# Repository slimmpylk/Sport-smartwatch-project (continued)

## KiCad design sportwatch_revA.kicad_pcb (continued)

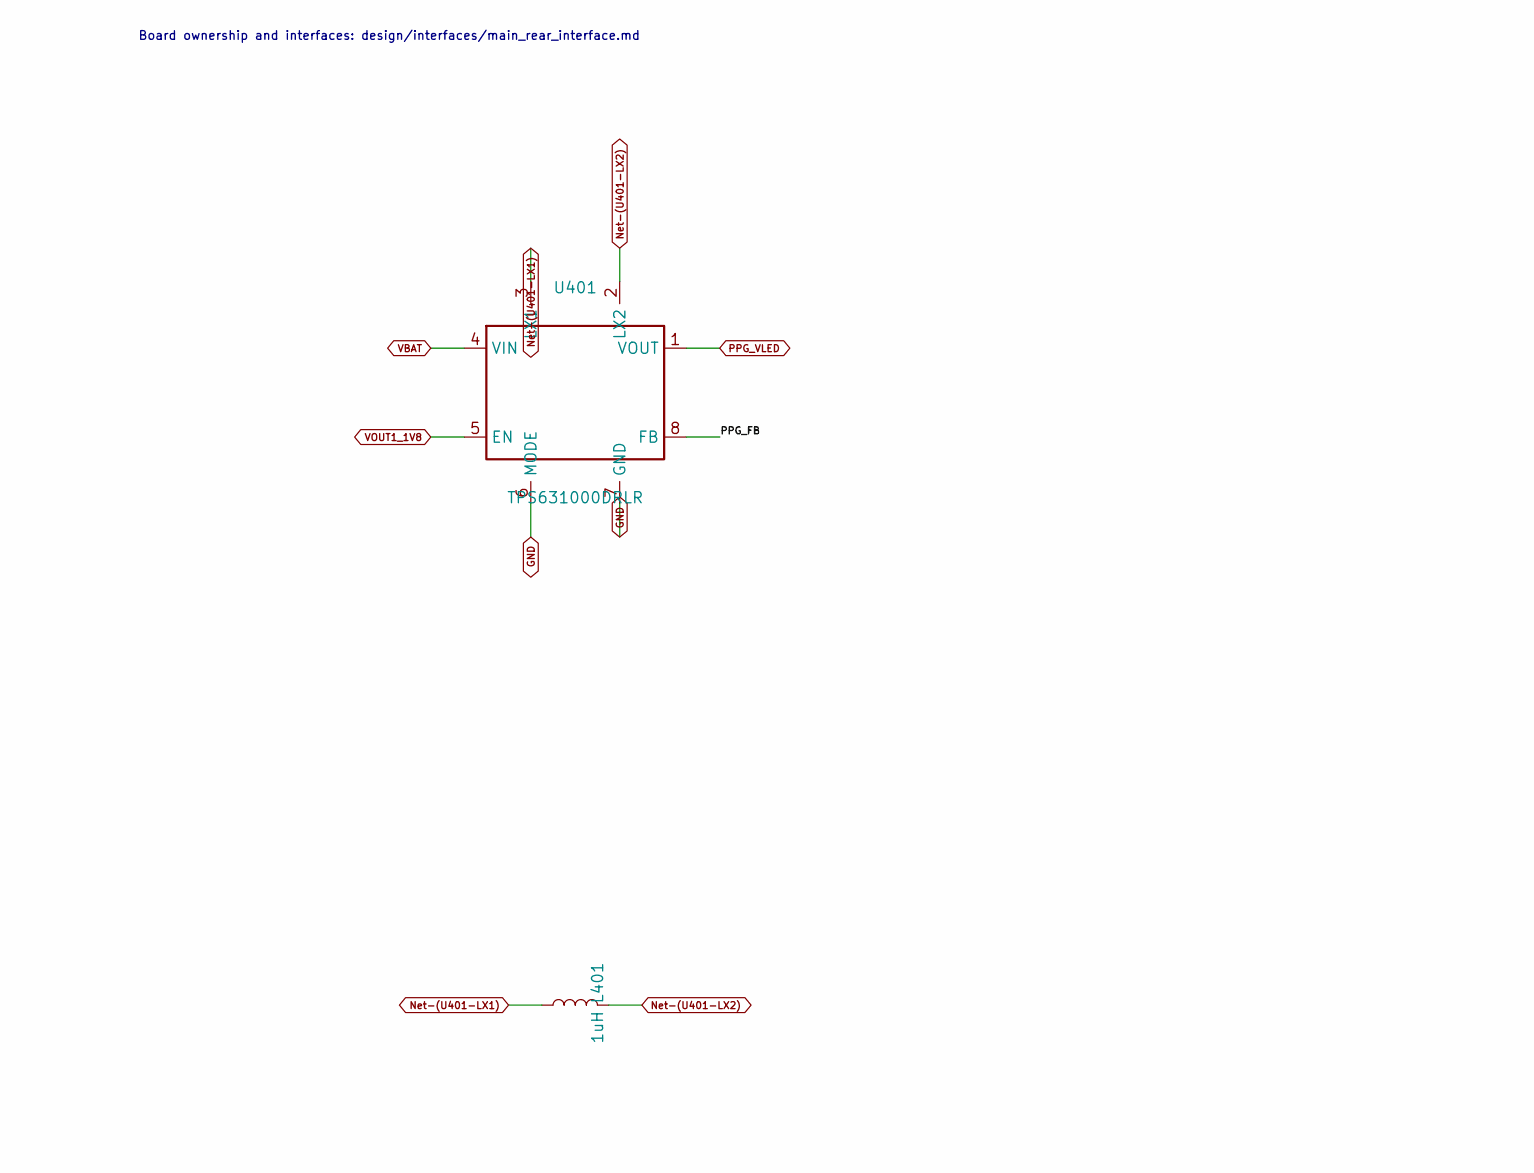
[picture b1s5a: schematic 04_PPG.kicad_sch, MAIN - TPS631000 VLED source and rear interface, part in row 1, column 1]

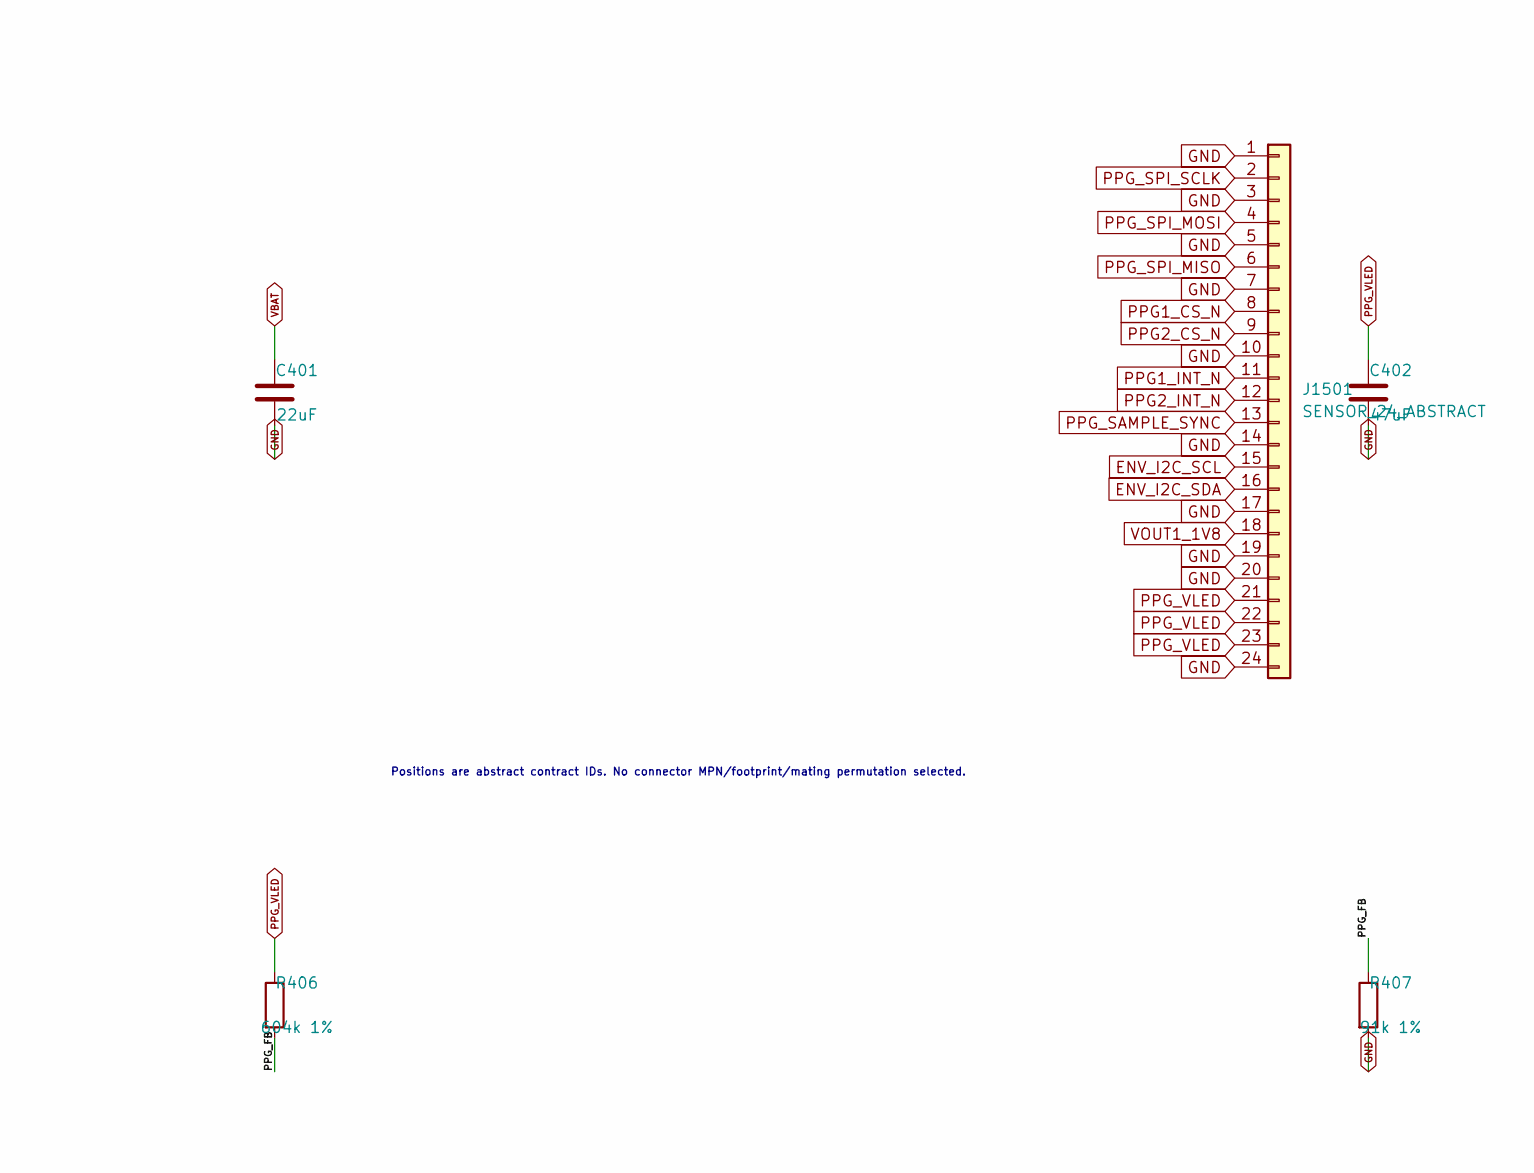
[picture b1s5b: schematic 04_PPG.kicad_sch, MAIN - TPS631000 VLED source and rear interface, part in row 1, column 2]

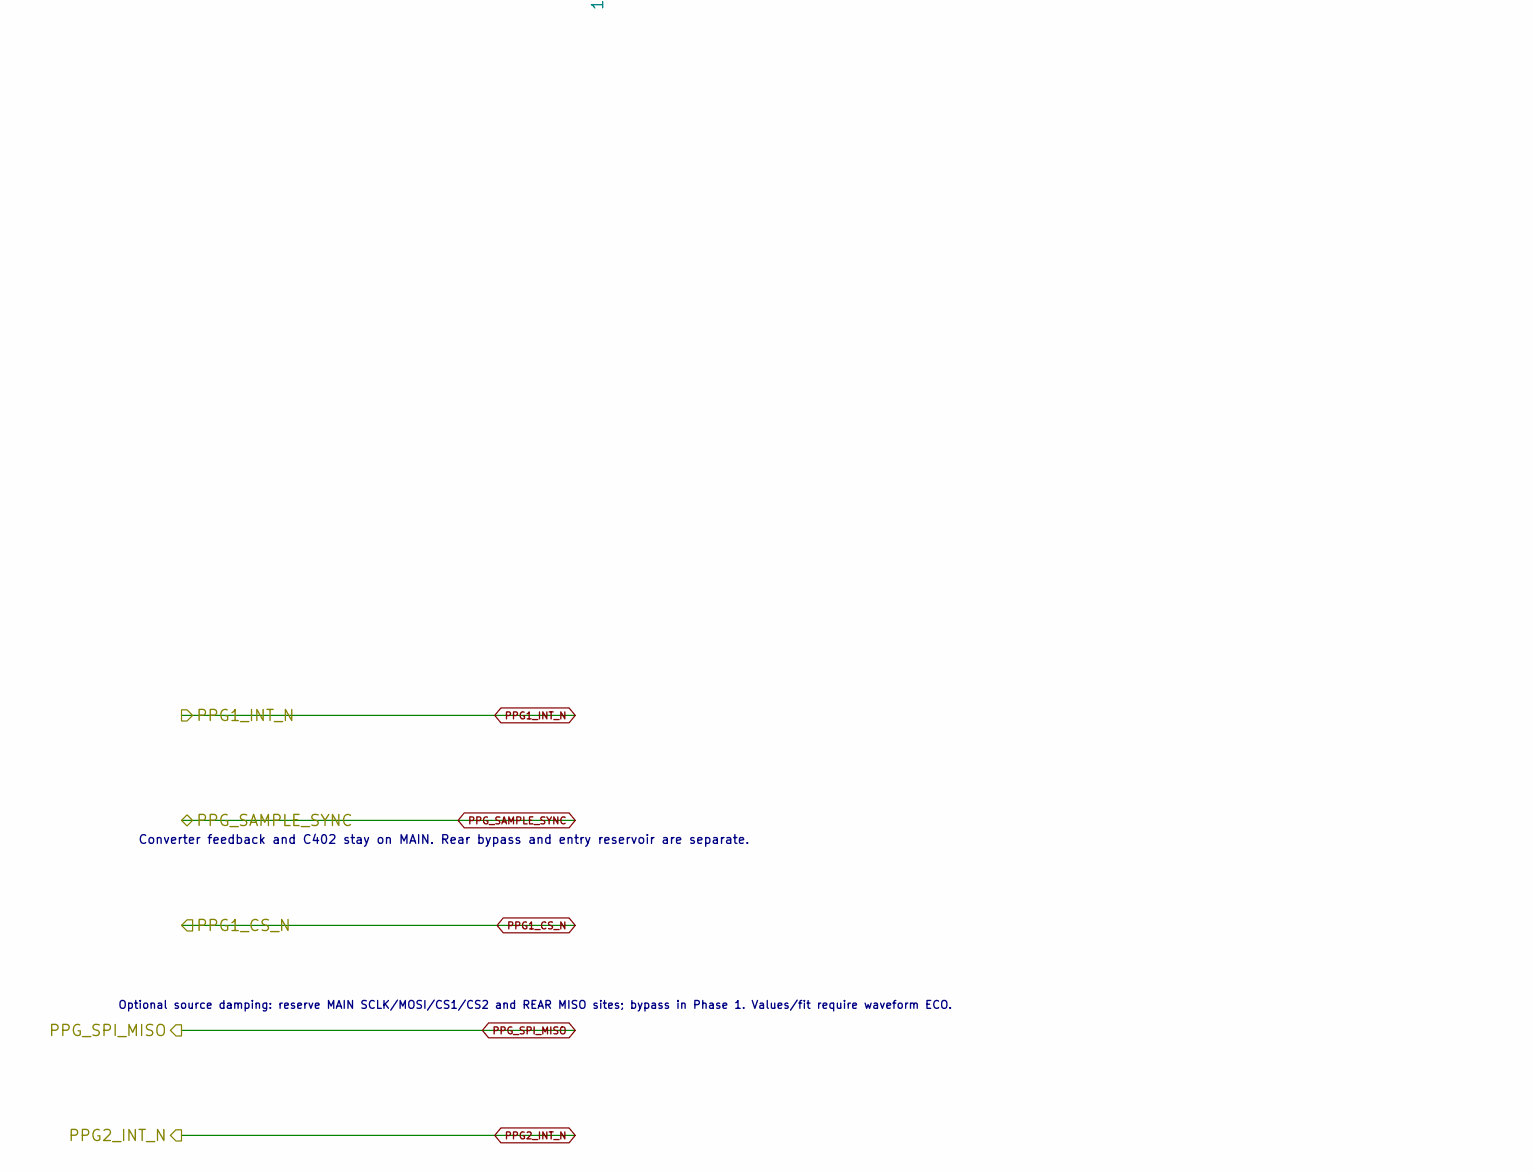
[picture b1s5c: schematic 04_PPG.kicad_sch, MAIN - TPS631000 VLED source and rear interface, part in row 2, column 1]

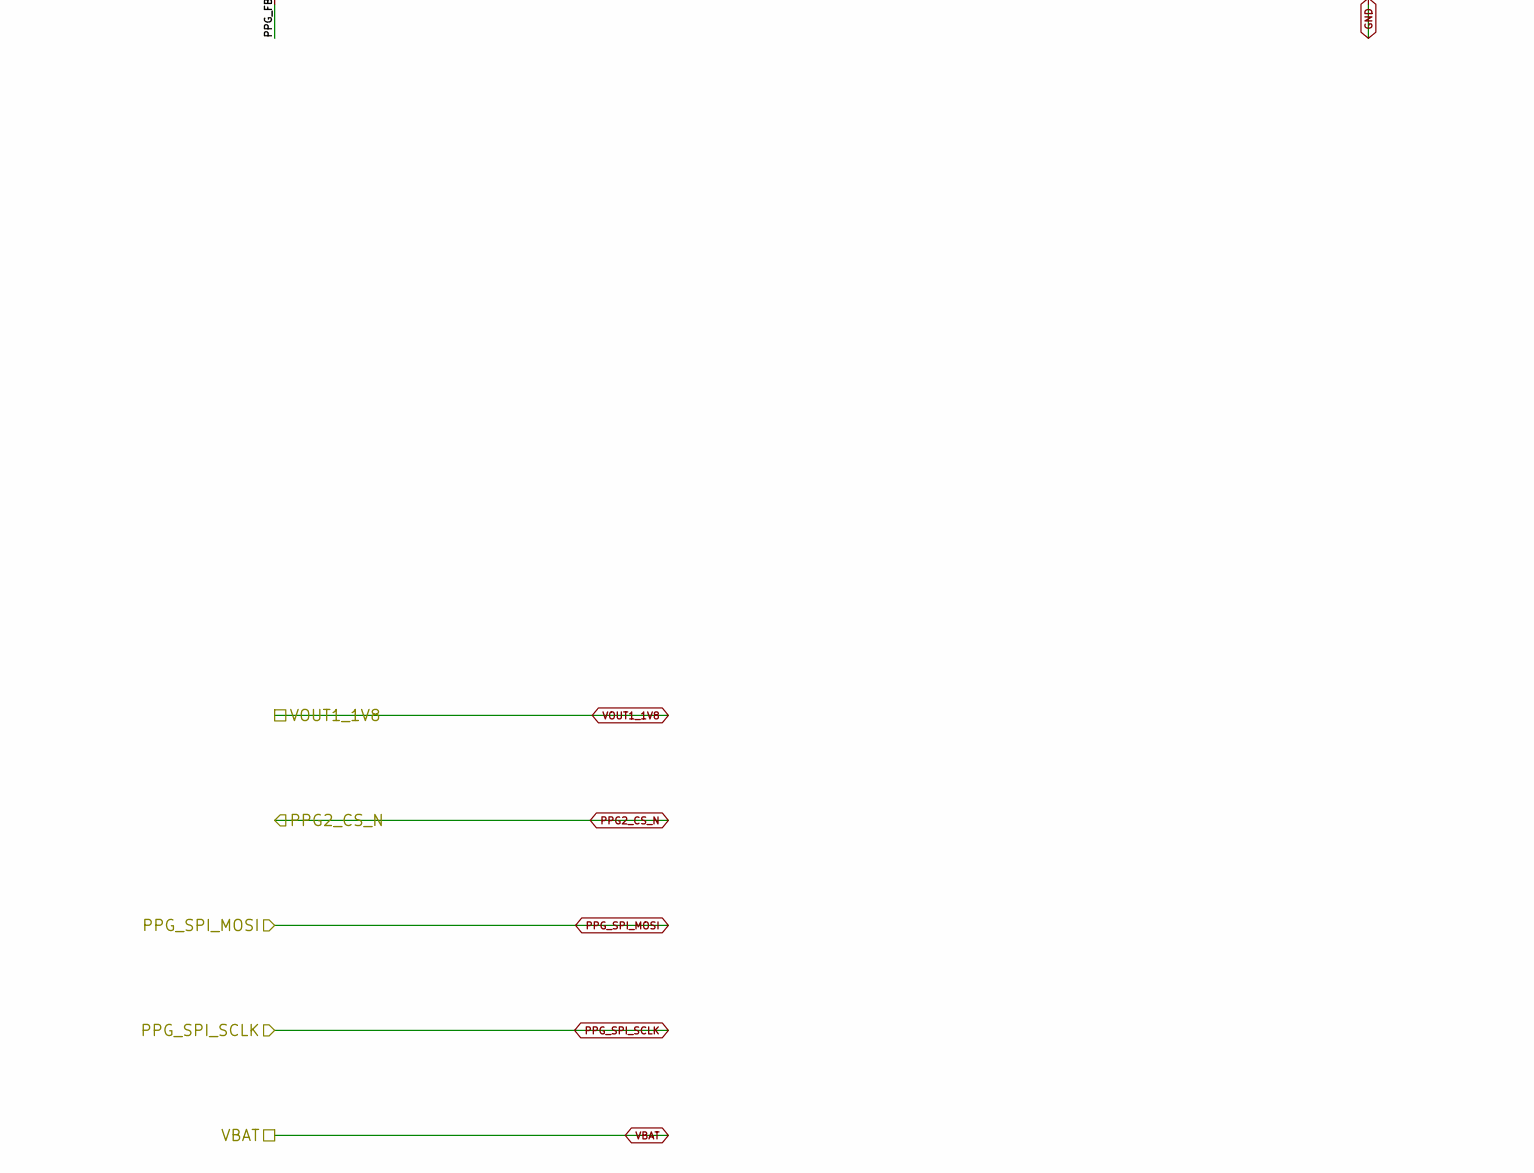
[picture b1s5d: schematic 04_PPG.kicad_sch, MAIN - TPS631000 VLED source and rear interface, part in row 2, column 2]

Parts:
C401: 22uF; C_0603_1608Metric
C402: 47uF; C_0805_2012Metric
J1501: SENSOR_24_ABSTRACT
L401: 1uH; L_2016_2016Metric
R406: 604k 1%; R_0402_1005Metric
R407: 91k 1%; R_0402_1005Metric
U401: TPS631000DRLR; SOT-583-8

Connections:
/04_PPG/PPG_FB: R406.2, R407.1, U401.8 (FB)
GND: C401.2, C402.2, J1501.1, J1501.3, J1501.5, J1501.7, J1501.10, J1501.14, J1501.17, J1501.19, J1501.20, J1501.24, R407.2, U401.6 (MODE), U401.7 (GND); also elsewhere on the board
unnamed: L401.1, U401.3 (LX1)
unnamed: L401.2, U401.2 (LX2)
PPG_VLED: C402.1, J1501.21, J1501.22, J1501.23, R406.1, U401.1 (VOUT)
VBAT: C401.1, U401.4 (VIN); also elsewhere on the board
VOUT1_1V8: J1501.18, U401.5 (EN); also elsewhere on the board

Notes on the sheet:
Board ownership and interfaces: design/interfaces/main_rear_interface.md
Converter feedback and C402 stay on MAIN. Rear bypass and entry reservoir are separate.
Positions are abstract contract IDs. No connector MPN/footprint/mating permutation selected.
Optional source damping: reserve MAIN SCLK/MOSI/CS1/CS2 and REAR MISO sites; bypass in Phase 1. Values/fit require waveform ECO.

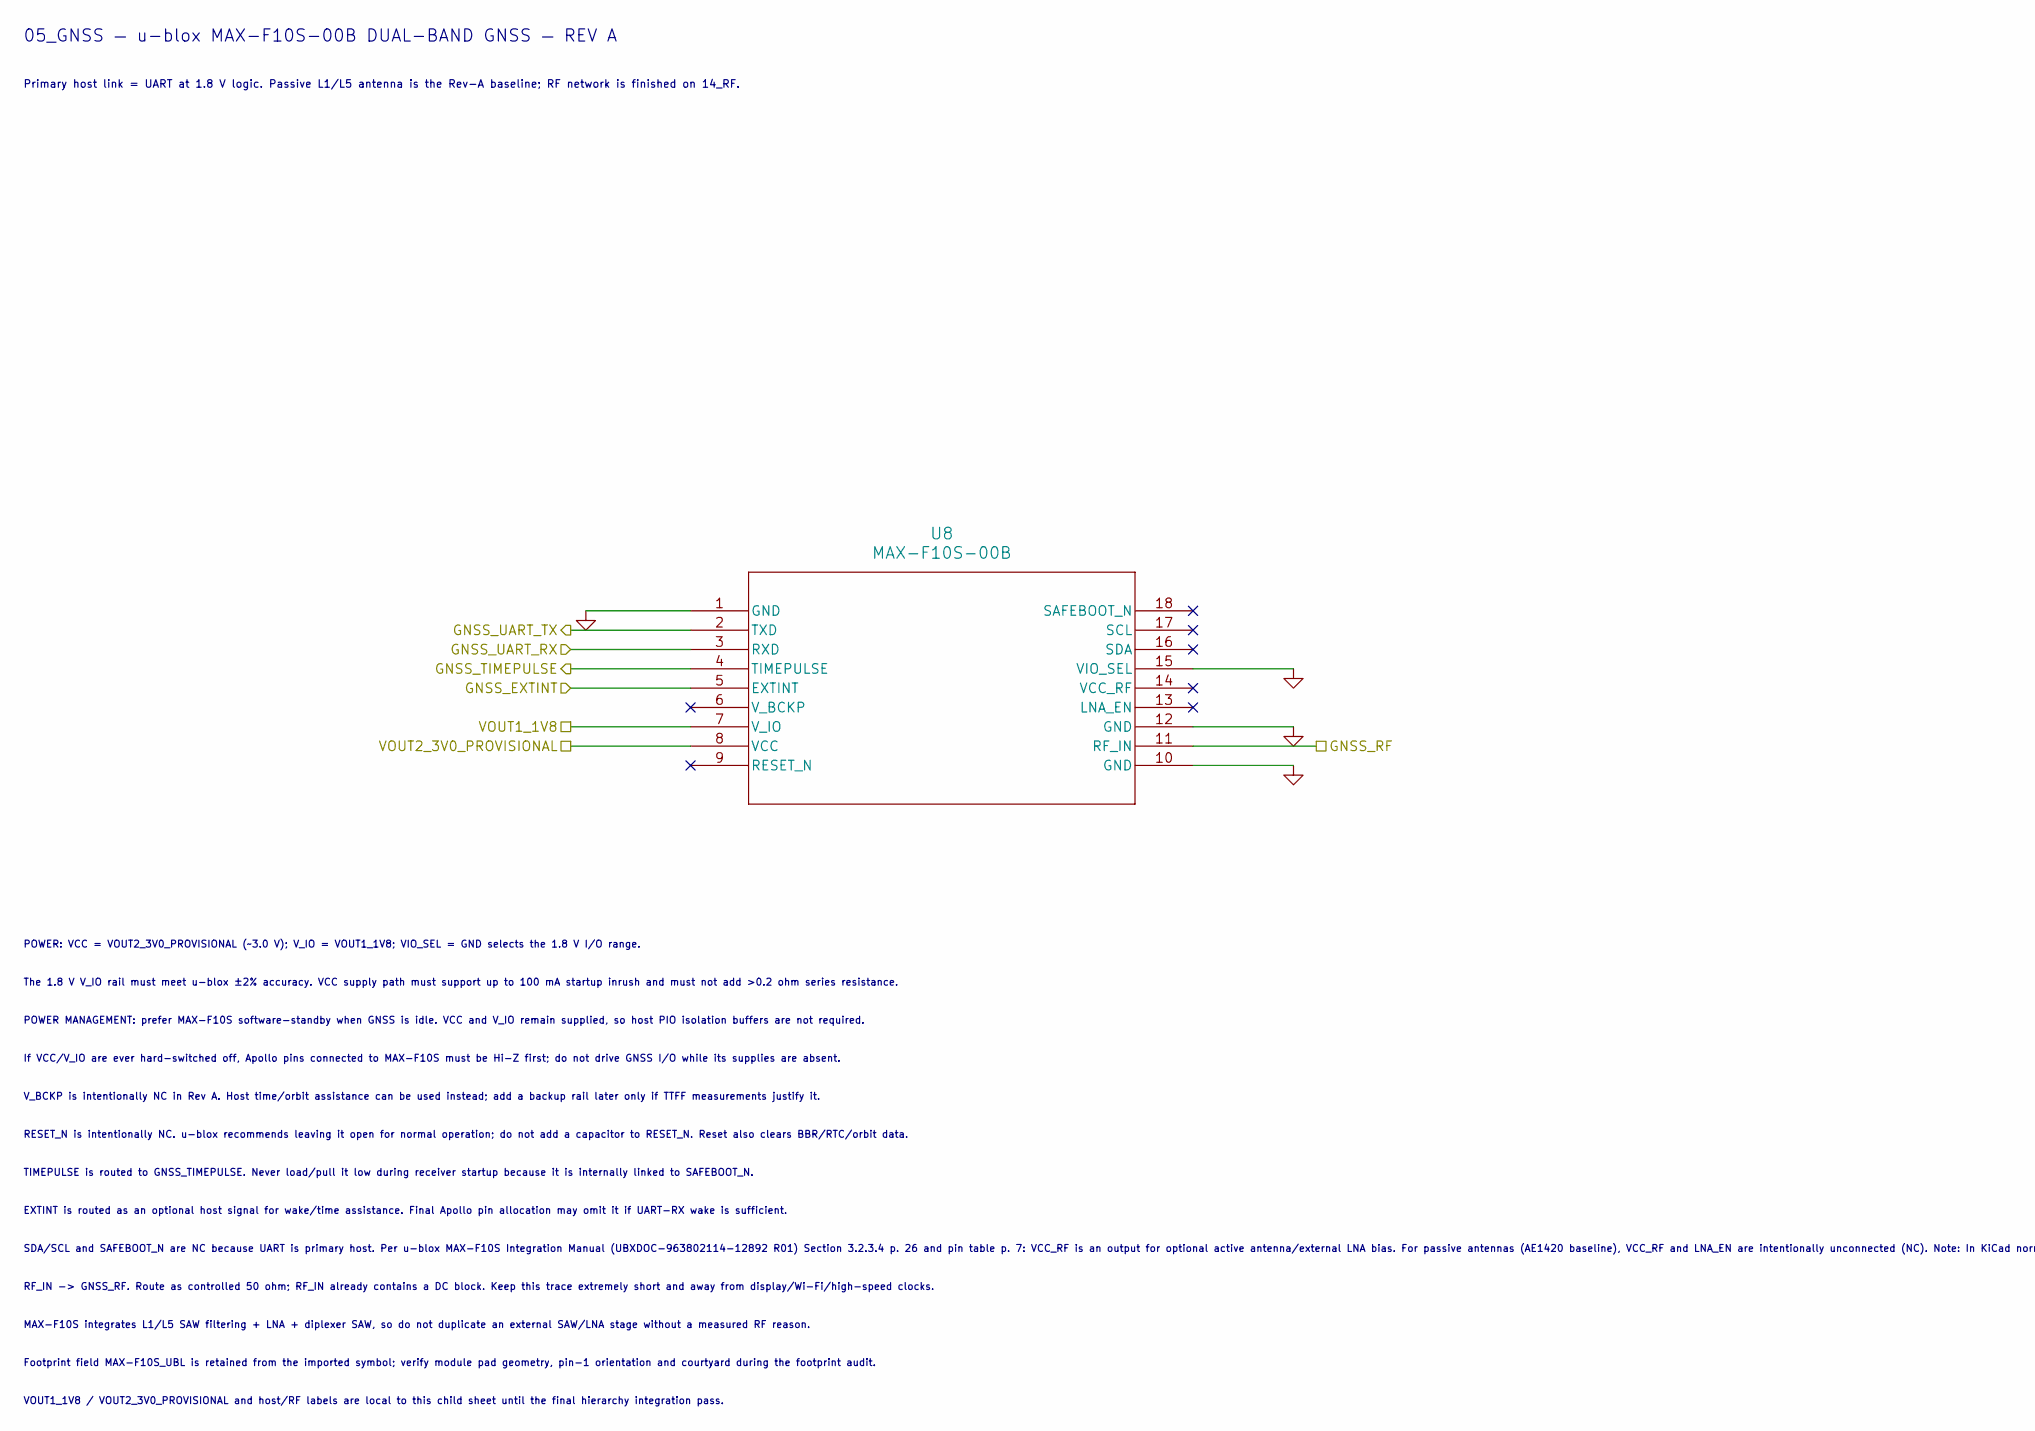
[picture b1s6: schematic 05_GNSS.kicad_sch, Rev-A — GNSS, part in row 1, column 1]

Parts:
U8: MAX-F10S-00B; MAX-F10S_UBL

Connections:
/GNSS_EXTINT: U8.5 (EXTINT); also elsewhere on the board
/GNSS_RF: U8.11 (RF_IN); also elsewhere on the board
/GNSS_TIMEPULSE: U8.4 (TIMEPULSE); also elsewhere on the board
/GNSS_UART_RX: U8.3 (RXD); also elsewhere on the board
/GNSS_UART_TX: U8.2 (TXD); also elsewhere on the board
/VOUT2_3V0_PROVISIONAL: U8.8 (VCC); also elsewhere on the board
GND: U8.1 (GND), U8.10 (GND), U8.12 (GND), U8.15 (VIO_SEL); also elsewhere on the board
VOUT1_1V8: U8.7 (V_IO); also elsewhere on the board

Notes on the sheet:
EXTINT is routed as an optional host signal for wake/time assistance. Final Apollo pin allocation may omit it if UART-RX wake is sufficient.
VOUT1_1V8 / VOUT2_3V0_PROVISIONAL and host/RF labels are local to this child sheet until the final hierarchy integration pass.
SDA/SCL and SAFEBOOT_N are NC because UART is primary host. Per u-blox MAX-F10S Integration Manual (UBXDOC-963802114-12892 R01) Section 3.2.3.4 p. 26 and pin table p. 7: VCC_RF is an output for optional active antenna/external LNA bias. For passive antennas (AE1420 baseline), VCC_RF and LNA_EN are 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
Primary host link = UART at 1.8 V logic. Passive L1/L5 antenna is the Rev-A baseline; RF network is finished on 14_RF.
If VCC/V_IO are ever hard-switched off, Apollo pins connected to MAX-F10S must be Hi-Z first; do not drive GNSS I/O while its supplies are absent.
The 1.8 V V_IO rail must meet u-blox ±2% accuracy. VCC supply path must support up to 100 mA startup inrush and must not add >0.2 ohm series resistance.
MAX-F10S integrates L1/L5 SAW filtering + LNA + diplexer SAW, so do not duplicate an external SAW/LNA stage without a measured RF reason.
RESET_N is intentionally NC. u-blox recommends leaving it open for normal operation; do not add a capacitor to RESET_N. Reset also clears BBR/RTC/orbit data.
RF_IN -> GNSS_RF. Route as controlled 50 ohm; RF_IN already contains a DC block. Keep this trace extremely short and away from display/Wi-Fi/high-speed clocks.
POWER: VCC = VOUT2_3V0_PROVISIONAL (~3.0 V); V_IO = VOUT1_1V8; VIO_SEL = GND selects the 1.8 V I/O range.
TIMEPULSE is routed to GNSS_TIMEPULSE. Never load/pull it low during receiver startup because it is internally linked to SAFEBOOT_N.
05_GNSS — u-blox MAX-F10S-00B DUAL-BAND GNSS — REV A
POWER MANAGEMENT: prefer MAX-F10S software-standby when GNSS is idle. VCC and V_IO remain supplied, so host PIO isolation buffers are not required.
Footprint field MAX-F10S_UBL is retained from the imported symbol; verify module pad geometry, pin-1 orientation and courtyard during the footprint audit.
V_BCKP is intentionally NC in Rev A. Host time/orbit assistance can be used instead; add a backup rail later only if TTFF measurements justify it.
